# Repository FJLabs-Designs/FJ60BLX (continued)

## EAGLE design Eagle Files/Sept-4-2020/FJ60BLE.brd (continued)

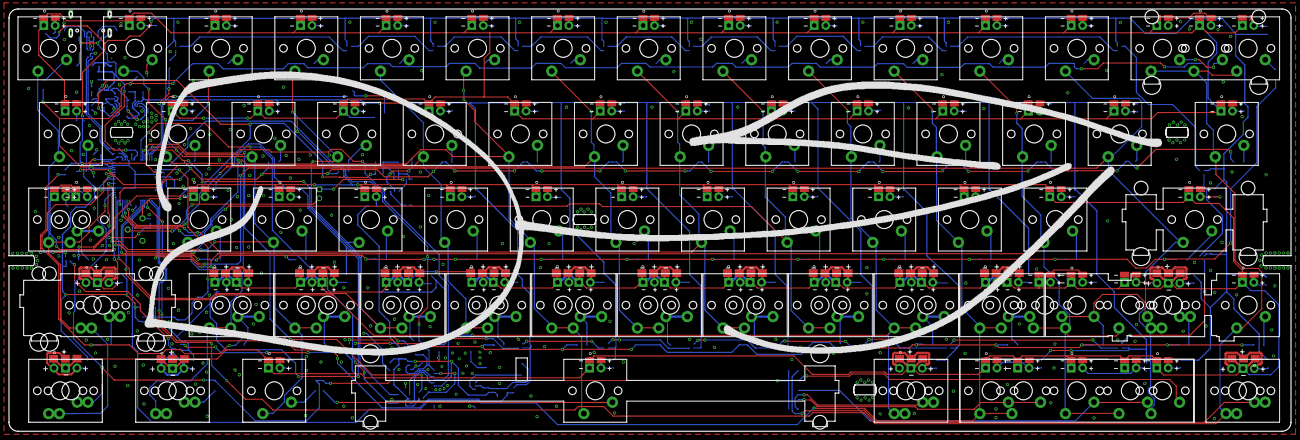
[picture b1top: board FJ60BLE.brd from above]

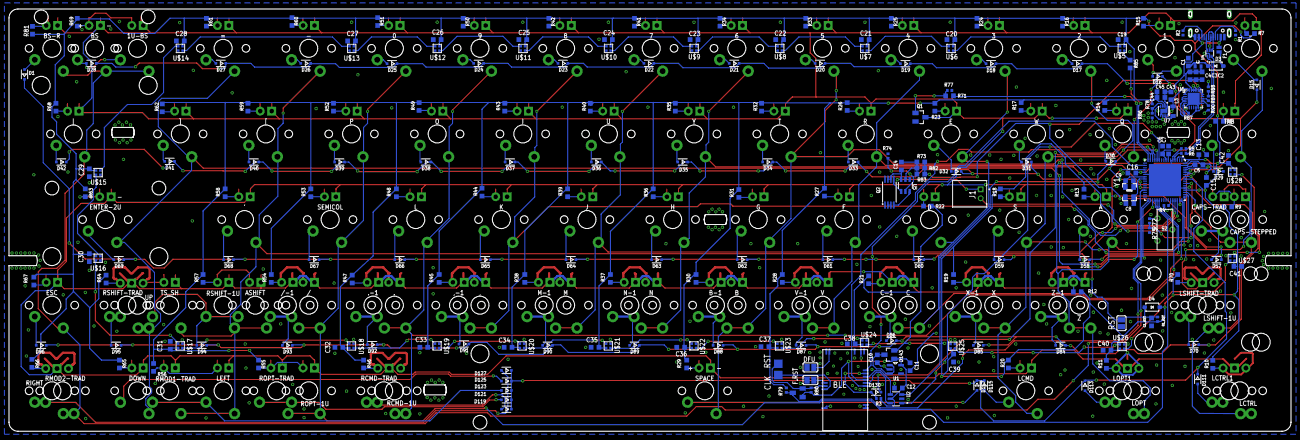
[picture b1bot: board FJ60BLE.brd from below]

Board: 2 copper layers, 285.2 x 94.0 mm, 424 parts (250 on the bottom side), 227 nets.

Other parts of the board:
U$3: FJLABSLOGO
U$4: FJ60BLXV1.0
U$93: WHITE_TULIP

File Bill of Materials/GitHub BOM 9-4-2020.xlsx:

Qty | Value | Device | Package | Parts | Description | Technology | Manufacturer Part # | LCSC Part # | LCSC Link
66 |  | DIODE-SOD323-R | SOD323-R | D1, D15, D16, D17, D18, D19, D20, D21, D22, D23, D24, D25, D26, D27, D28, D29, 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 | 1N4148WS-7-F SMD Diode. SOD323-R Package [not flat leads] | SMD | 1N4148WS-7-F | C60580 | https://lcsc.com/product-detail/Switching-Diode_DIODES_1N414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
2 | 100K | RESISTOR-0405 | R0402 | R86, R90 | 100K 0402 Resistor | SMD | RC-02W104JT | C280907 | https://lcsc.com/product-detail/Chip-Resistor-Surface-Mount_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
28 | 100nF | CAPACITOR-0603 | C0603 | C1_RST, C4, C5, C14, C19, C20, C21, C22, C23, C24, C25, C26, C27, C28, C29, C30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 | 100nF 0603 Capacitor | SMD | TCC0603X7R104K500CT | C282519 | https://lcsc.com/product-detail/Multilayer-Ceramic-Capacitor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
7 | 10K | RESISTOR-0405 | R0402 | R1_RST, R3, R75, R77, R79, R80, R87 | 10K 0402 Resistor | SMD | RC-02W1002FT | C258091 | https://lcsc.com/product-detail/Chip-Resistor-Surface-Mount_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
9 | 10uF | CAPACITOR-0603 | C0603 | C1, C2, C11, C13, C15, C16, C43, C44, C45 | 10uF 0603 Capacitor | SMD | CL10A106MQ8NNNC | C1691 | https://lcsc.com/product-detail/Multilayer-Ceramic-Capacitor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
1 | 120Ω @ 100MHz | BLM15HB221SN1 | 402 | L2 | 120Ohm @ 100MHz 600mA Ferrite Bead | SMD | FCM1005KF-121T06 | C304241 | https://lcsc.com/product-detail/Ferrite-Beads_TAITEC-FCM1005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
2 | 12pF | CAPACITOR-0603 | C0603 | C8, C9 | 12pF 0603 Capacitor | SMD | 0603CG120J500NT | C1642 | https://lcsc.com/product-detail/Multilayer-Ceramic-Capacitor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
4 | 1K | RESISTOR-0405 | R0402 | R4, R74, R88, R89 | 1K 0402 Resistor | SMD | RC-02W1001FT | C226166 | https://lcsc.com/product-detail/Chip-Resistor-Surface-Mount_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
5 | 1uF | CAPACITOR-0603 | C0603 | C3, C6, C7, C10, C12 | 1uF 0603 Capacitor | SMD | 0603X105K160NT | C89188 | https://lcsc.com/product-detail/Multilayer-Ceramic-Capacitor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
1 | 1uH | L_CHIP-0805(2012-METRIC) | INDC2009X120 | L3 | 1uH 0805 Inductor, >1A, <150mΩ ESR | SMD | CMH201209B1R0MT | C394956 | https://lcsc.com/product-detail/Power-Inductors_FH-Guangdong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
2 | 22 | RESISTOR-0405 | R0402 | R5, R6 | 22ohm 0402 Resistor [USB Data] | SMD | RC-02W22R0FT | C304591 | https://lcsc.com/product-detail/Chip-Resistor-Surface-Mount_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
1 | 270K | RESISTOR-0405 | R0402 | R78 | 270K 0402 Resistor | SMD | RC-02W274JT | C321418 | https://lcsc.com/product-detail/Chip-Resistor-Surface-Mount_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
70 | 300 | RESISTOR-0603 | R0603 | R7, R8, R9, R10, R11, R12, R13, R14, R15, R16, R17, R18, R19, R20, R21, R22, R2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 | 300ohm 0603 Resistor | SMD | RK73H1JTTD3000F | C139055 | https://lcsc.com/product-detail/Chip-Resistor-Surface-Mount_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
2 | 5.1K | RESISTOR-0405 | R0402 | R1, R2 | 5.1K 0402 Resistor | SMD | RTT025R10FTH | C103115 | https://lcsc.com/product-detail/Chip-Resistor-Surface-Mount_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
1 | 7.2K | RESISTOR-0405 | R0402 | R72 | 7.5K 0402 Resistor | SMD | 0402WGF7501TCE | C25918 | https://lcsc.com/product-detail/Chip-Resistor-Surface-Mount_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
1 | 8MHz | CRYSTAL-4PIN-3.2X2.5 | CRYSTAL-3.2X2.5 | Y1 | 8MHz 10pF 4-Pad Crystal | SMD | TAXM8M4RDBCCT2T | C400090 | https://lcsc.com/product-detail/SMD-Crystal-Resonators_TAE-Z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
1 | AT90USB646 | AT90USB1286-MU | QFN50P900X900X100-65N | U3 | AT90USB646 Microcontroller, QFN NoLeads Package | SMD | AT90USB646-MU | Microchip AT90USB646-MU: https://www.microchip.com/wwwproducts/en/AT90USB646
1 | BSS138 | BSS138 | SOT-23 | U$1 | BSS138 N Channel MOSFET for SWRST Level Shift | SMD | BSS138 | C427380 | https://lcsc.com/product-detail/MOSFET_MDD-Microdiode-Electr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
1 | FDN337N | FDN337N | SSOT-3 | Q1 | N-Channel MOSFET | SMD | FDN337N | C475694 | https://lcsc.com/product-detail/New-Quadratic-Unclassified-D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
1 | FS312F-G | FS312F-G | FS312F-G | U5 | Battery Protection IC FS312F-G | SMD | FS312F-G | C82736 | https://lcsc.com/product-detail/Battery-Protection-ICs_FS312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
1 | FS8205A | FS8205A | SOP65P640X120-8N | Q2 | Dual N-Channel MOSFET | SMD | FS8205A | C16052 | https://lcsc.com/product-detail/MOSFET_Fortune-Semicon-FS820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
2 | MBR0520LT1G | CESD5V0D1 | SOD-123 | D3, D4 | 20V 500mA Schottky Diode | SMD | MBR0520LT1G | C23848 | https://lcsc.com/product-detail/Schottky-Barrier-Diodes-SBD_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
1 | MCP73871-2AAI/ML | MCP73871-2AAI/ML | QFN50P400X400X100-21N | U6 | MCP73871-2AAI/ML Battery Charging IC with Power Path Management | SMD | MCP73871-2AAI/ML | C144351 | https://lcsc.com/product-detail/PMIC-Battery-Management_Micr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
1 | MDBT40-NO-EXTRAMDBT40-NO-EXTRA | MDBT40-NO-EXTRAMDBT40-NO-EXTRA | MDBT40-NO-EXTRA | BLE | MDBT40 from Adafruit with Adafruit Firmware | SMD | MDBT40-256RV3 | Raytac MDBT40-256V3: https://www.raytac.com/product/ins.php?index_id=63
1 | MF-MSMF075-2 | CAPC1210X112N1210 | CAPC1210X112N | F1 | PTC Fuse for up to 1A 5V | SMD | MF-MSMF075-2 | C84140 | https://lcsc.com/product-detail/Surface-Mount-Fuses_BOURNS_M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
1 | MIC5205-3.3YM5TR | MIC5205-3.3YM5TR | SOT95P280X130-5N | U1 | Generic 3.3V Fixed Output LDO | SMD | ME6212C33M5G | C81233 | https://lcsc.com/product-detail/Dropout-Regulators-LDO_MICRO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
1 | PMEG2005CT | PMEG2005CT | SOT23 | D143 | Dual Schottky Barrier Diode, 20V.500mA | SMD | PMEG2005CT,215 | C282562 | https://lcsc.com/product-detail/Schottky-Barrier-Diodes-SBD_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
1 | S2B-PH-K-S(LF)(SN) | S2B-PH-K-S(LF)(SN) | JST_S2B-PH-K-S(LF)(SN) | J1 | JST PH 2.0 [2 pin] Battery Connector, Right Angle, Through Hole | THT | S2B-PH-K-S(LF)(SN) | C173752 | https://lcsc.com/product-detail/Wire-To-Board-Wire-To-Wire-C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
24 | SK6805 | SK6805 | SK6805 | U$5, U$6, U$7, U$8, U$9, U$10, U$11, U$12, U$13, U$14, U$15, U$16, U$17, U$18, 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 | SK6805 equivalent Addressable RGB LED's | SMD | DY-S1515065/RGBC/6805-5T | C524053 | https://lcsc.com/product-detail/Light-Emitting-Diodes-LED_TO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
1 | SN74LVC2G34DBVR | SN74LVC2G34DBVR | SOT95P280X145-6N | U2 | 5V to 3.3V Level Shifter Dual Channel | THT | SN74LVC2G34DBVR | C347589 | https://lcsc.com/product-detail/Logic-Buffers-Drivers-Receiv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
1 | SSSS213000 | SSSS213000 | SSSS213000 | S2 | Switch Slide Spdt 300ma 6v | SMD | SSSS213000 | C125054 | https://lcsc.com/product-detail/Toggle-Switches_ALPS-Electri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
1 | TPS61252DSGT | TPS61252DSGT | SON50P200X200X80-9N | U7 | TPS61252DSGR/T Boost Converter IC | SMD | TPS61252DSGR | C128617 | https://lcsc.com/product-detail/DC-DC-Converters_Texas-Instr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
1 | USB-C | USB-C | TYPE-C-31-M-12 | USB-C | USB C Port | SMD/THT | TYPE-C-31-M-12 | C165948 | https://lcsc.com/product-detail/USB-Type-C_Korean-Hroparts-E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
1 | USBLC6-2P6 | USBLC6-2P6 | SOT50P160X60-6N | U4 | USB ESD Protection Diode with Powerline Protection | SMD | USBLC6-2P6 | C15999 | https://lcsc.com/product-detail/Diodes-ESD_STMicroelectronic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
64 | LED-0805 | LED-0805 | LED0805 | U$29, U$30, U$31, U$32, U$33, U$34, U$35, U$36, U$37, U$38, U$39, U$40, U$41, U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 | White 0805 SMD LED | SMD | ORH-W45A | C205447 | https://lcsc.com/product-detail/Light-Emitting-Diodes-LED_08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 | ASSEMBLE ON ONLY ONE BOARD

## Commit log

2020-08-29 Added component analysis
2020-08-29 removed DSStore
2020-08-29 Added License
2020-08-29 Added README
2020-08-29 Screwed up readme format
2020-09-07 Added Sept. 4th Version as manufactured
2020-09-07 Added some README info
